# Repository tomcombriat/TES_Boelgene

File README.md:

# TES - Bølgene

Bølgene is a digital instrument inspired by the [Ondes Martenot](https://en.wikipedia.org/wiki/Ondes_Martenot), a contemporary instrument to the Theremin.
The original instrument features a force sensitive button for the expression/volume and continuous pitch controlled by the position of a ring.

Bølgene is a small, table-top, digital, instrument having the base features. The main differences is that it features polyphony, with several pressure sensitive buttons.

Bølgene (first version) was created in a few weeks specially for [Oslo Skaper Festival 2024](https://norwaymakers.org/osf24). 

## v1

### Hardware

Nothing special here except a well sized plank, found in the street. Apart from that…
 - CPU: RP2040
 - additionnal ADC: MCP3008
 - DAC: PT8211
 - expressions buttons: 4
 - synthesis potentiometers:

Made on single sided PCB.

### Software
 - sound system: [Mozzi](https://sensorium.github.io/Mozzi/)

#### boelgene_1

The version presented at Oslo Skaper Festival, monophonic with Delay Feedback creating weird sounds, especially in the bass register.

#### boelgene_poly 

Version supporting 4 expression buttons, currently tuned to the fifth and the two thirds. Uses the same synthesis algorithm than boelgene_v1

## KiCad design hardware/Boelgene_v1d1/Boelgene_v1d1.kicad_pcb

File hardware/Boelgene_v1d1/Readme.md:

# Building instructions and details

This document contains details and building information for Bølgene v1.1.

## General information

This version of Bølgene is a small step from the v1 which was based on a one-sided PCB.
As the previous version, this is based on a Raspberry Pico (RP2040) MCU and a PT8211 DAC. Because of the low number of analog inputs on the RP2040, a companion ADC is also used.

## Audio modes

The PCB supports three audio modes:

 - PWM straight from the RP2040. Resolution is 12bits. All DAC components can then be omitted (PT8211, C9, C10, C11 and C12) and normally C2, C3 and R1.
 - mono output: components for the PWM can be omitted (C7 and C8) and components for the right channel (C10, C12). This outputs a 16bits signal on `out_dac1`.
 - stereo output: components for the PWM can be omitted (C7 and C8). This outputs a 16bits signal on `out_dac1` and `out_dac2`.
 
All outputs do not have volume control as of the PCB. An external log potentiometer can be adjucted.

## Analog inputs

There are a few analog signals that are measured:

### Pressure (touch):

These are measured wih the help of resisor dividers (RV1-4) and are to be connected to force sensitive resistors (range 1.5kg, ref in BOM). The pots are adjusting the sensitivity of the pressure sensors.

## Ribbon

This is to be connected to the central pin of a 10 turns, 10k linear potentiometer. The other two pins should be connected to GNDA and ADC_ref. 

## Synthesis input

There are currently 5 potentiometers to adjust the synthesis parameters. There is a free slot so a sixth could be added.

The test points labelled pot1-5 are to be connected to the central pin (10k linear), and the other two to GNDA and ADC_ref.

## Power

As of now, the system is powered by four AA batteries giving a nominal voltage of 4*1.2 = 4.8V. The only limitation there are the IC voltage tolerances: RP2040 is given fine up to 6V, PT8211 up to 7V.

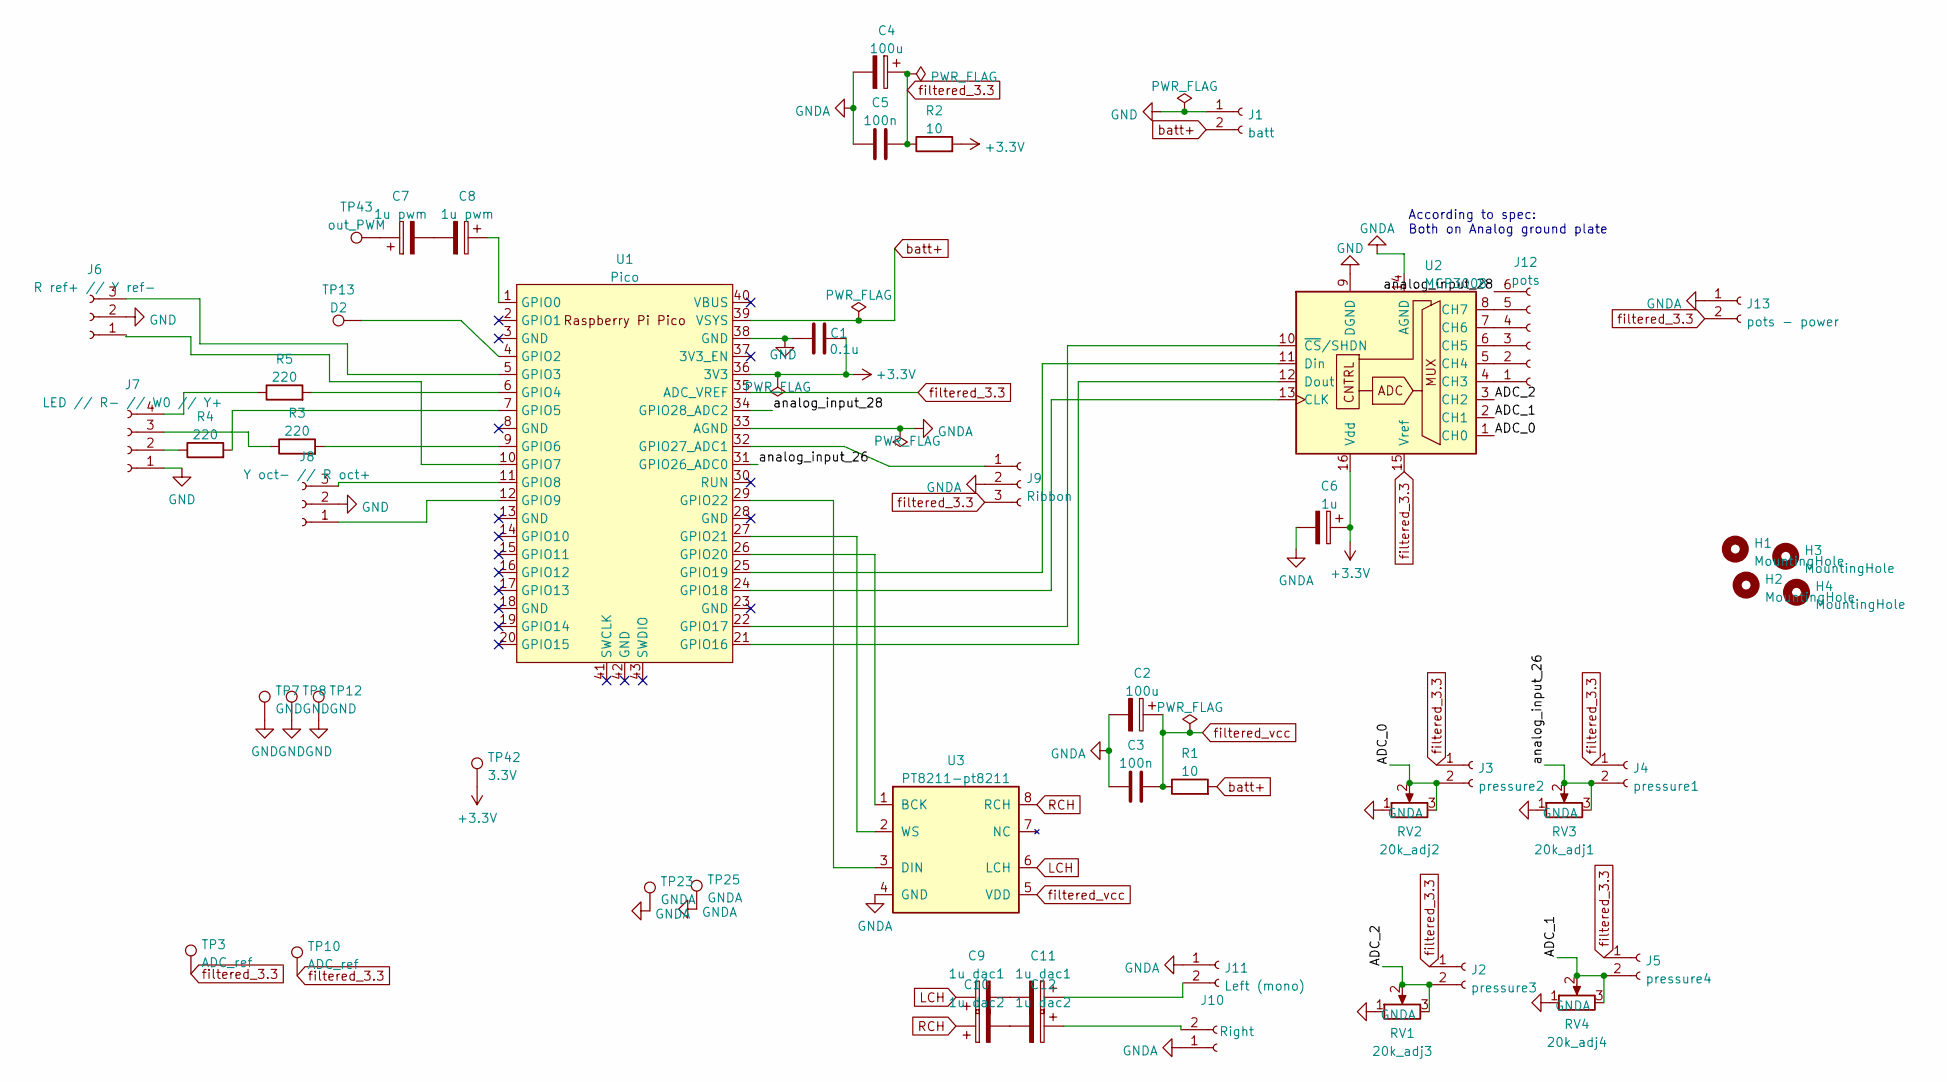
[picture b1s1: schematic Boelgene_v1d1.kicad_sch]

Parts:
C1: 0.1u; C_Axial_L3.8mm_D2.6mm_P7.50mm_Horizontal
C2, C4: 100u; CP_Radial_D8.0mm_P5.00mm
C3, C5: 100n; C_Axial_L3.8mm_D2.6mm_P7.50mm_Horizontal
C6: 1u; CP_Radial_D5.0mm_P2.00mm
C7, C8: 1u pwm; CP_Radial_D5.0mm_P2.50mm
C9, C11: 1u dac1; CP_Radial_D5.0mm_P2.50mm
C10, C12: 1u dac2; CP_Radial_D5.0mm_P2.50mm
H1, H2, H3, H4: MountingHole; MountingHole_3.2mm_M3
J1: batt; JST_XH_B2B-XH-A_1x02_P2.50mm_Vertical
J2: pressure3; JST_XH_B2B-XH-A_1x02_P2.50mm_Vertical
J3: pressure2; JST_XH_B2B-XH-A_1x02_P2.50mm_Vertical
J4: pressure1; JST_XH_B2B-XH-A_1x02_P2.50mm_Vertical
J5: pressure4; JST_XH_B2B-XH-A_1x02_P2.50mm_Vertical
J6: R ref+ // Y ref-; JST_PH_B3B-PH-K_1x03_P2.00mm_Vertical
J7: LED // R- // W0 // Y+; JST_PH_B4B-PH-K_1x04_P2.00mm_Vertical
J8: Y oct- // R oct+; JST_PH_B3B-PH-K_1x03_P2.00mm_Vertical
J9: Ribbon; JST_PH_B3B-PH-K_1x03_P2.00mm_Vertical
J10: Right; JST_XH_B2B-XH-A_1x02_P2.50mm_Vertical
J11: Left (mono); JST_XH_B2B-XH-A_1x02_P2.50mm_Vertical
J12: pots; JST_PH_B6B-PH-K_1x06_P2.00mm_Vertical
J13: pots - power; JST_XH_B2B-XH-A_1x02_P2.50mm_Vertical
R1, R2: 10; R_Axial_DIN0207_L6.3mm_D2.5mm_P7.62mm_Horizontal
R3, R4, R5: 220; R_Axial_DIN0207_L6.3mm_D2.5mm_P7.62mm_Horizontal
RV1: 20k_adj3; Potentiometer_Runtron_RM-065_Vertical
RV2: 20k_adj2; Potentiometer_Runtron_RM-065_Vertical
RV3: 20k_adj1; Potentiometer_Runtron_RM-065_Vertical
RV4: 20k_adj4; Potentiometer_Runtron_RM-065_Vertical
TP3, TP10: ADC_ref; TestPoint_THTPad_2.0x2.0mm_Drill1.0mm
TP7, TP8, TP12: GND; TestPoint_THTPad_2.0x2.0mm_Drill1.0mm
TP13: D2; TestPoint_THTPad_2.0x2.0mm_Drill1.0mm
TP23, TP25: GNDA; TestPoint_THTPad_2.0x2.0mm_Drill1.0mm
TP42: 3.3V; TestPoint_THTPad_2.0x2.0mm_Drill1.0mm
TP43: out_PWM; TestPoint_THTPad_2.0x2.0mm_Drill1.0mm
U1: Pico; RPi_Pico_TH
U2: MCP3008; DIP-16_W7.62mm
U3: PT8211-pt8211; SOP-8_3.9x4.9mm_P1.27mm

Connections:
+3.3V: C1.2, C6.1, R2.2, TP42.1, U1.36 (3V3), U2.16 (Vdd)
/ADC_0: J3.2, RV2.2, RV2.3, U2.1 (CH0)
/ADC_1: J5.2, RV4.2, RV4.3, U2.2 (CH1)
/ADC_2: J2.2, RV1.2, RV1.3, U2.3 (CH2)
/analog_input_26: J4.2, RV3.2, RV3.3, U1.31 (GPIO26_ADC0)
/analog_input_28: J12.6, U1.34 (GPIO28_ADC2)
GND: C1.1, J1.1, J6.2, J7.1, J8.2, TP7.1, TP8.1, TP12.1, U1.38 (GND), U2.9 (DGND)
GNDA: C2.2, C3.2, C4.2, C5.2, C6.2, J9.2, J10.1, J11.1, J13.1, RV1.1, RV2.1, RV3.1, RV4.1, TP23.1, TP25.1, U1.33 (AGND), U2.14 (AGND), U3.4 (GND)
LCH: C9.1, U3.6 (LCH)
unnamed: C7.1, TP43.1
unnamed: C7.2, C8.2
unnamed: C8.1, U1.1 (GPIO0)
unnamed: C10.2, C12.2
unnamed: C11.1, J11.2
unnamed: C9.2, C11.2
unnamed: C12.1, J10.2
unnamed: J6.1, U1.10 (GPIO7)
unnamed: J6.3, U1.5 (GPIO3)
unnamed: J7.2, R4.1
unnamed: J7.3, R3.1
unnamed: J7.4, R5.1
unnamed: J8.1, U1.12 (GPIO9)
unnamed: J8.3, U1.11 (GPIO8)
unnamed: J9.1, U1.32 (GPIO27_ADC1)
unnamed: J12.1, U2.4 (CH3)
unnamed: J12.2, U2.5 (CH4)
unnamed: J12.3, U2.6 (CH5)
unnamed: J12.4, U2.7 (CH6)
unnamed: J12.5, U2.8 (CH7)
unnamed: R3.2, U1.9 (GPIO6)
unnamed: R4.2, U1.7 (GPIO5)
unnamed: R5.2, U1.6 (GPIO4)
unnamed: TP13.1, U1.4 (GPIO2)
unnamed: U1.21 (GPIO16), U2.12 (Dout)
unnamed: U1.22 (GPIO17), U2.10 (~CS/SHDN)
unnamed: U1.24 (GPIO18), U2.13 (CLK)
unnamed: U1.25 (GPIO19), U2.11 (Din)
unnamed: U1.26 (GPIO20), U3.1 (BCK)
unnamed: U1.27 (GPIO21), U3.2 (WS)
unnamed: U1.29 (GPIO22), U3.3 (DIN)
RCH: C10.1, U3.8 (RCH)
batt+: J1.2, R1.2, U1.39 (VSYS)
filtered_3.3: C4.1, C5.1, J2.1, J3.1, J4.1, J5.1, J9.3, J13.2, R2.1, TP3.1, TP10.1, U1.35 (ADC_VREF), U2.15 (Vref)
filtered_vcc: C2.1, C3.1, R1.1, U3.5 (VDD)

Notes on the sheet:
According to spec: Both on Analog ground plate

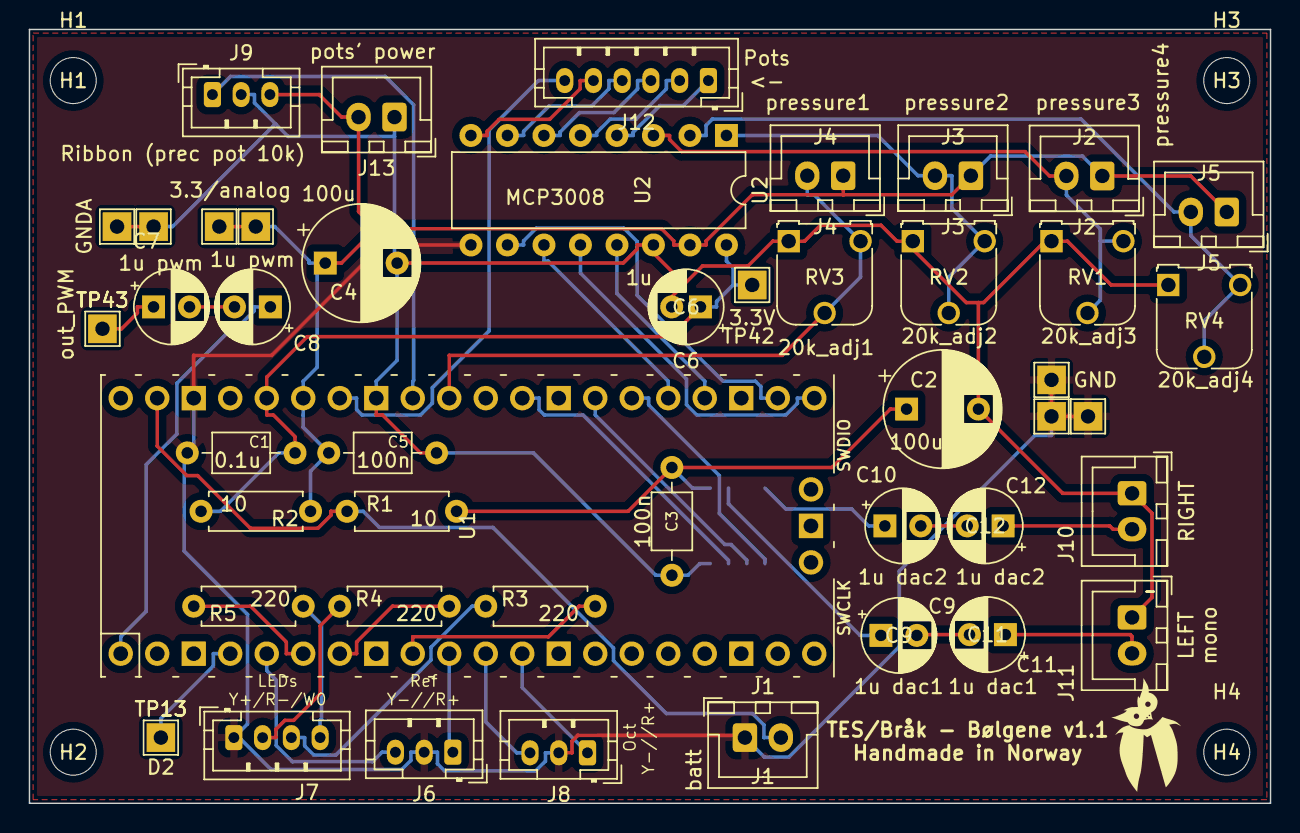
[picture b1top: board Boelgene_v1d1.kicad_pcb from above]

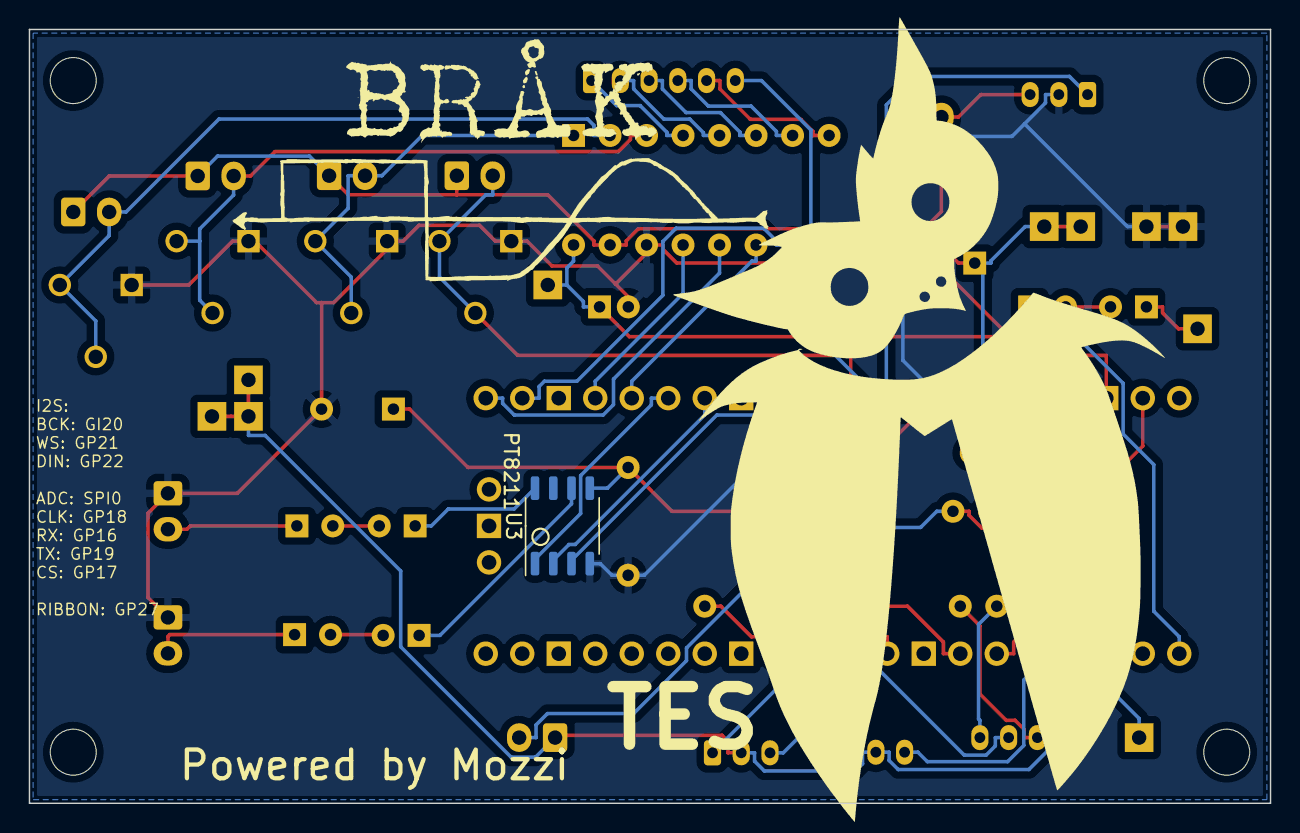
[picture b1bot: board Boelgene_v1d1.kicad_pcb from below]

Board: 2 copper layers, 86.4 x 53.8 mm, 52 parts (2 on the bottom side), 44 nets.

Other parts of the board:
G150: LOGO; owl_F_50x70

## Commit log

2024-09-25 Added kicad components
2024-09-25 Added initial kicad project
2024-09-25 Updated sch
2024-09-28 Started pcb
2024-09-28 Routing of pcb
2024-10-29 Updated PCB
2024-10-29 Added mono software
2024-10-29 Added simple copyright
2024-11-10 Added poly version of Boelgene software
2024-11-14 Modified software for poly
2025-01-21 Added gitignore
2025-01-21 Version 1.1 of hardware
2025-01-21 Actual version 1.1
2025-01-21 Removed unneeded files
2025-01-21 Update after zone filling
2025-01-21 Added gerber export
2025-01-21 Added automatically generated Bom
2025-01-22 Added BOM
2025-01-22 Added correct ribbon input reference
2025-01-22 Updated gerber
2025-01-22 Added pt8211 sym
2025-01-22 Added readme
2025-01-22 Added details in readme
2025-01-29 Added FM synth for Boelgene
2025-02-01 Updated bom
2025-02-01 Started anti-aliasing study script
2025-02-02 Finished aliasing frequency calculator
2025-02-03 Implemented anti-alias algorithm
2025-02-04 Added BiPotBoost
2025-02-04 "Added BiPotBoost, cleanup"
2025-02-04 Updated the mappers to new version of FixMath
2025-02-06 Added calibration script
2025-02-06 Calibrated pressure for full range
2025-02-06 Updated comments
2025-02-06 Optimized BiPot
2025-02-21 Added free modulation mode
2025-02-24 Fixed headroom
2025-02-26 Added LUT generator for easier free FM tuning
2025-02-26 Added FMRatio LUT to ease landing on int/half int ratio
2025-03-30 Updated PCB with connectors
2025-04-05 Added TH Pico model
2025-04-08 Added brak logo
2025-04-08 Added Mozzi ref
2025-04-17 Added visual cue for FMisNOTdead
2025-09-17 First tries on Formant synthesis
    Added noise to formant synth
2025-09-17 Update after new comp
2025-09-20 Progressive bpf with vol
2025-09-21 Modularization, cleanup
2025-09-21 Added sq Oscillator
2025-09-21 Put global param in own struct
2025-09-22 Saw as bass
2025-09-25 Added AM modulation
2025-10-06 Added 3D CAD for proto v2
2025-10-06 Updated Snak
2025-10-07 Added Wiring guide
2025-10-08 Started fingerboard drawing
2025-10-08 Better axis
2025-10-08 Added OnOff holder
2025-10-08 Changed to fretboard with moveable holes
2025-10-09 More options for fingerboard
2025-10-09 Added symbols
2025-10-14 Added config for proto v2
2025-10-14 Mapping for proto v2
2025-10-17 Proto v2 moved to PWM
2025-10-19 Better config for v2
2025-10-24 Adapted snak to v2
